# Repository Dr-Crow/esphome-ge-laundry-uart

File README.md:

# ESPHome GE Laundry UART

Local Home Assistant control and monitoring for compatible GE appliances through ESPHome and the appliance's GEA serial bus.

> [!WARNING]
> The appliance uses an 8P8C modular connector that looks like Ethernet, but it is **not Ethernet**. Do not connect it to network equipment.

**Scanned a Rev 3K, 3L or 3M board?** Match the revision printed on the carrier and the C3 or C6 marking on the XIAO. Unplug the appliance cable before attaching USB. The compact boards are review prototypes. [Open the compact firmware and service guide](https://github.com/Dr-Crow/esphome-ge-laundry-uart/blob/90f50558ca8f220444624ddab47f50d685d8c828/firmware/shared-rev3c/README.md)

The project began as an effort to integrate a GE washer and dryer with Home Assistant. An ESP32 powered by the appliance communication port reports information such as remaining time and cycle completion through ESPHome. Early work involved researching the GEA2 and GEA3 protocols and the U+ Connect module; later, [GE Appliances](https://github.com/geappliances) and [FirstBuild](https://firstbuild.com/inventions/home-assistant-adapter/) published additional hardware and protocol information. The maintained ESPHome implementation now lives in [mguaylam/esphome-gea](https://github.com/mguaylam/esphome-gea), while this repository provides compatible hardware, reference configurations, manufacturing files, and enclosures.

## Getting started

### I already have a board

For Rev 2.x, follow the [firmware setup guide](firmware/README.md) to choose a GEA2 or GEA3 configuration, flash the board, connect it to Home Assistant, and check the status LEDs. The [Rev 2 enclosure](case/rev2/README.md) includes ready-to-print files.

### I want to order a board

Start with [PCB Rev 2.2](pcb/rev2.2/README.md), then follow the [step-by-step ordering guide](pcb/ORDERING.md). Rev 2.2 corrects the known Rev 2.0 and Rev 2.1 board-file problems.

**Current status:** Rev 2.2 is the recommended manufacturing candidate; physical testing is still pending. A JLCPCB quote checked on September 19, 2026 was **$78.07 before shipping and tax for five fully assembled boards**, or about **$15.61 per board**. Prices and component availability can change.

Older boards and the complete change history are listed in the [PCB revision index](pcb/README.md). Hardware contributors should also read the [contribution guide](CONTRIBUTING.md).

## Related projects

- [GE Appliances organization](https://github.com/geappliances)
- [FirstBuild Home Assistant adapter](https://firstbuild.com/inventions/home-assistant-adapter/)
- [puddly/casserole](https://github.com/puddly/casserole)
- [GEMakers/green-bean](https://github.com/GEMakers/green-bean)
- [doitaljosh/gea-interface-board](https://github.com/doitaljosh/gea-interface-board)
- [doitaljosh/ge-appliances-re](https://github.com/doitaljosh/ge-appliances-re)
- [doitaljosh/geabus-documentation](https://github.com/doitaljosh/geabus-documentation)
- [simbaja/gehome](https://github.com/simbaja/gehome)
- [GE Appliances Home Assistant adapter](https://github.com/geappliances/home-assistant-adapter)
- [GE Appliances Home Assistant examples](https://github.com/geappliances/home-assistant-examples)
- [GE Appliances Home Assistant bridge](https://github.com/geappliances/home-assistant-bridge)

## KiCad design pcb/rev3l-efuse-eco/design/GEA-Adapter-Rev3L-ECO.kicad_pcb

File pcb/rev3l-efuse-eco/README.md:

# Rev 3L-E shared eFuse output bypass study

Experimental 65 × 30 mm carrier for isolated prototype evaluation. The underside is marked **3L-E / PROTOTYPE**. Use 3L-E to evaluate one relatively inexpensive change on the full-diagnostics carrier. The shared capacitor still has two vias in each output path. Electrical qualification, factory review and a 3L-E quote remain open.

[Native KiCad project](design/GEA-Adapter-Rev3L-ECO.kicad_pro) · [Schematic](design/GEA-Adapter-Rev3L-ECO.kicad_sch) · [Board](design/GEA-Adapter-Rev3L-ECO.kicad_pcb) · [Top CAM](evidence/cam-top.png) · [Bottom CAM](evidence/cam-bottom.png)

## What changed

C31 adds a 10 µF, 50 V, 1206 Samsung CL31A106KBHNNNE between the common protected input and ground. It uses C9’s existing C13585 SKU. C9 and C10 remain at the buck. R18 and R33 moved, with their original values. The board retains all 3L probe points, J7, signal selectors, both power inputs, front-only placement and the original outline. The two probe labels affected by placement moved with no reduction in text size.

| Center-to-center PCB route | U9 | U10 |
| --- | ---: | ---: |
| Previous closest fitted output capacitor C9, straight-line lower bound | 24.74 mm | 18.24 mm |
| New route from OUT pin 6 to C31 positive, horizontal copper including travel in end lands | 8.29 mm | 7.73 mm |
| Vias in this route | 2 | 2 |
| GND pin 8 to its nearest connected ground via | 1.94 mm | 2.43 mm |
| Plane-path straight-line lower bound between that via and C31’s ground via | 4.37 mm | 5.91 mm |

C31’s ground land reaches its ground via in 1.27 mm. Horizontal lengths exclude barrel depth. Ground current spreads through filled copper. These geometrical measurements establish proximity only. TI recommends local transient suppression at OUT. The residual two-via loop on each channel makes a separate capacitor per output preferable if the shared part does not keep both pins within their transient limits. [TI TPS25947, sections 5.1 and 8.3.1](https://www.ti.com/lit/ds/symlink/tps25947.pdf)

The +5 V detour adds 0.205 mm at the original 0.90 mm width on In2. This adds about 0.26 mΩ at 15.2 µm finished copper and 20 °C, or 0.16 mV at 0.60 A, using 1.724×10⁻⁸ Ω·m. The existing BOOT trace adds 0.027 mm at its original 0.205 mm width. Small sections of the receiver, input-overvoltage sense and priority-control signals were rerouted. The inner ground pours were refilled. The original rail-screen and mesh results belong to their original boards.

## Capacitance and qualification

Samsung’s 25 °C, 1 kHz, 1 V measurement curve gives typical effective capacitance of 3.386 µF at 12 V, 2.548 µF at 15 V, 1.898 µF at 18.85 V and 1.794 µF at 19.673 V by linear interpolation. The last voltage is a divider screen using the 1.223 V maximum rising OVLO threshold, 1.01 MΩ upper resistor, 67.32 kΩ lower resistor and 100 nA pin leakage. Handover, Q1 on the auxiliary divider and input-step overshoot require separate checks. Temperature, tolerance, aging and measurement amplitude can affect the installed capacitance. [Samsung characteristics](https://product.samsungsem.com/mlcc/CL31A106KBHNNN.do) · [TI electrical characteristics](https://www.ti.com/lit/ds/symlink/tps25947.pdf#page=9)

- On an isolated, current-limited fixture, measure the effective capacitance at operating bias and temperature. Capture each OUT at its IC ground with low-inductance probing during short-circuit interruption and hot-plug, including cable impedance and the highest enabled input. Record amplitude and duration. Design for margin to the continuous and transient absolute limits. TI’s −0.8 V OUT exception applies only below 1 µs.
- Check PIN1-only and PIN3-only start, priority transfer in both directions, a weak input still inside the voltage window, converter startup and module resets with both XIAO variants. Include the added charge taken by C31. R34/R41 set approximately 1.01 A nominal ILIM. The 0.60 A scenario is a load screen. AUXOFF indicates valid priority input after startup and can remain asserted during load overcurrent or thermal shutdown.
- Keep the entire appliance harness disconnected during USB programming. JP3 opens the D11 buck feed. The data steering paths and common ground remain. U11 is **ProTek SRV05-4-P-T7, C85364**. Its native datasheet link was corrected. J1 pins 4, 5 and 7 reach its steering diodes before the external series resistors. A powered data line can raise the module 5 V rail even with JP3 cut. Characterize each signal alone and together using representative source impedances and an initially unpowered carrier. Measure rail rise and injection current before any connector or protection redesign. See the separate data-line options for the residual pull-up paths and unqualified floating-REF proposal. [ProTek datasheet](https://www.lcsc.com/datasheet/C85364.pdf) · [Data-line protection choices](../compact-review/DATA-LINE-PROTECTION.md)
- Check USB-only cold attach on both modules. C11 and the five 100 nF capacitors contribute 10.5 µF nominal before the module’s load. D18 and D20 protect raw inputs upstream of the eFuses. A shorted TVS or sustained reversed harness depends on source-side current limiting. Check enclosed temperature, C3 antenna-lead routing, C6 antenna clearance and printed-case fit on both builds.

## Assembly evidence

Compared with combined commit `c7e102aaa9c85a485478ee5c403a945064977d56`, the bill goes from 72 to 73 fitted references and stays at 32 distinct LCSC codes. All 73 placements are on top. Only R18 and R33 change amongst previously fitted placements. Five fully assembled boards add five capacitor placements, with no additional distinct feeder SKU at these substitutions. No vendor fee or price is established for this ECO.

KiCad 9.0.9 reports zero ERC and DRC violations, zero unconnected items and zero schematic parity differences. Geometry editing used pcbnew 9.0.2. The corrected placement generator checks each fitted body center within 0.10 mm, including the rotated jack and headers. C31, R18 and R33 have body-edge distances of 9.05, 7.23 and 6.34 mm respectively. The 18 inherited bodies under JLC’s 2.5 mm guideline include the jack. Factory handling, tooling, copper tolerances and placement rotation still need the supplier’s review. [Body-edge audit](evidence/component-body-edge.csv) · [ERC](evidence/ERC.json) · [DRC and parity](evidence/DRC.json)

The CAM package contains four copper layers, 180 front paste objects and zero rear paste objects. The outline and nonplated holes match the parent. Rear QR artwork decoded from the new CAM rendering to the project repository. Physical scanning, powered testing and factory acceptance remain open. Board SHA-256 is `a03f99733d337c358b6f3299e666f42263c3d8cb844dea6cbb286324a991fa12`. [CAM and placement comparison](evidence/manufacturing-comparison.json) · [Review exports](manufacturing)

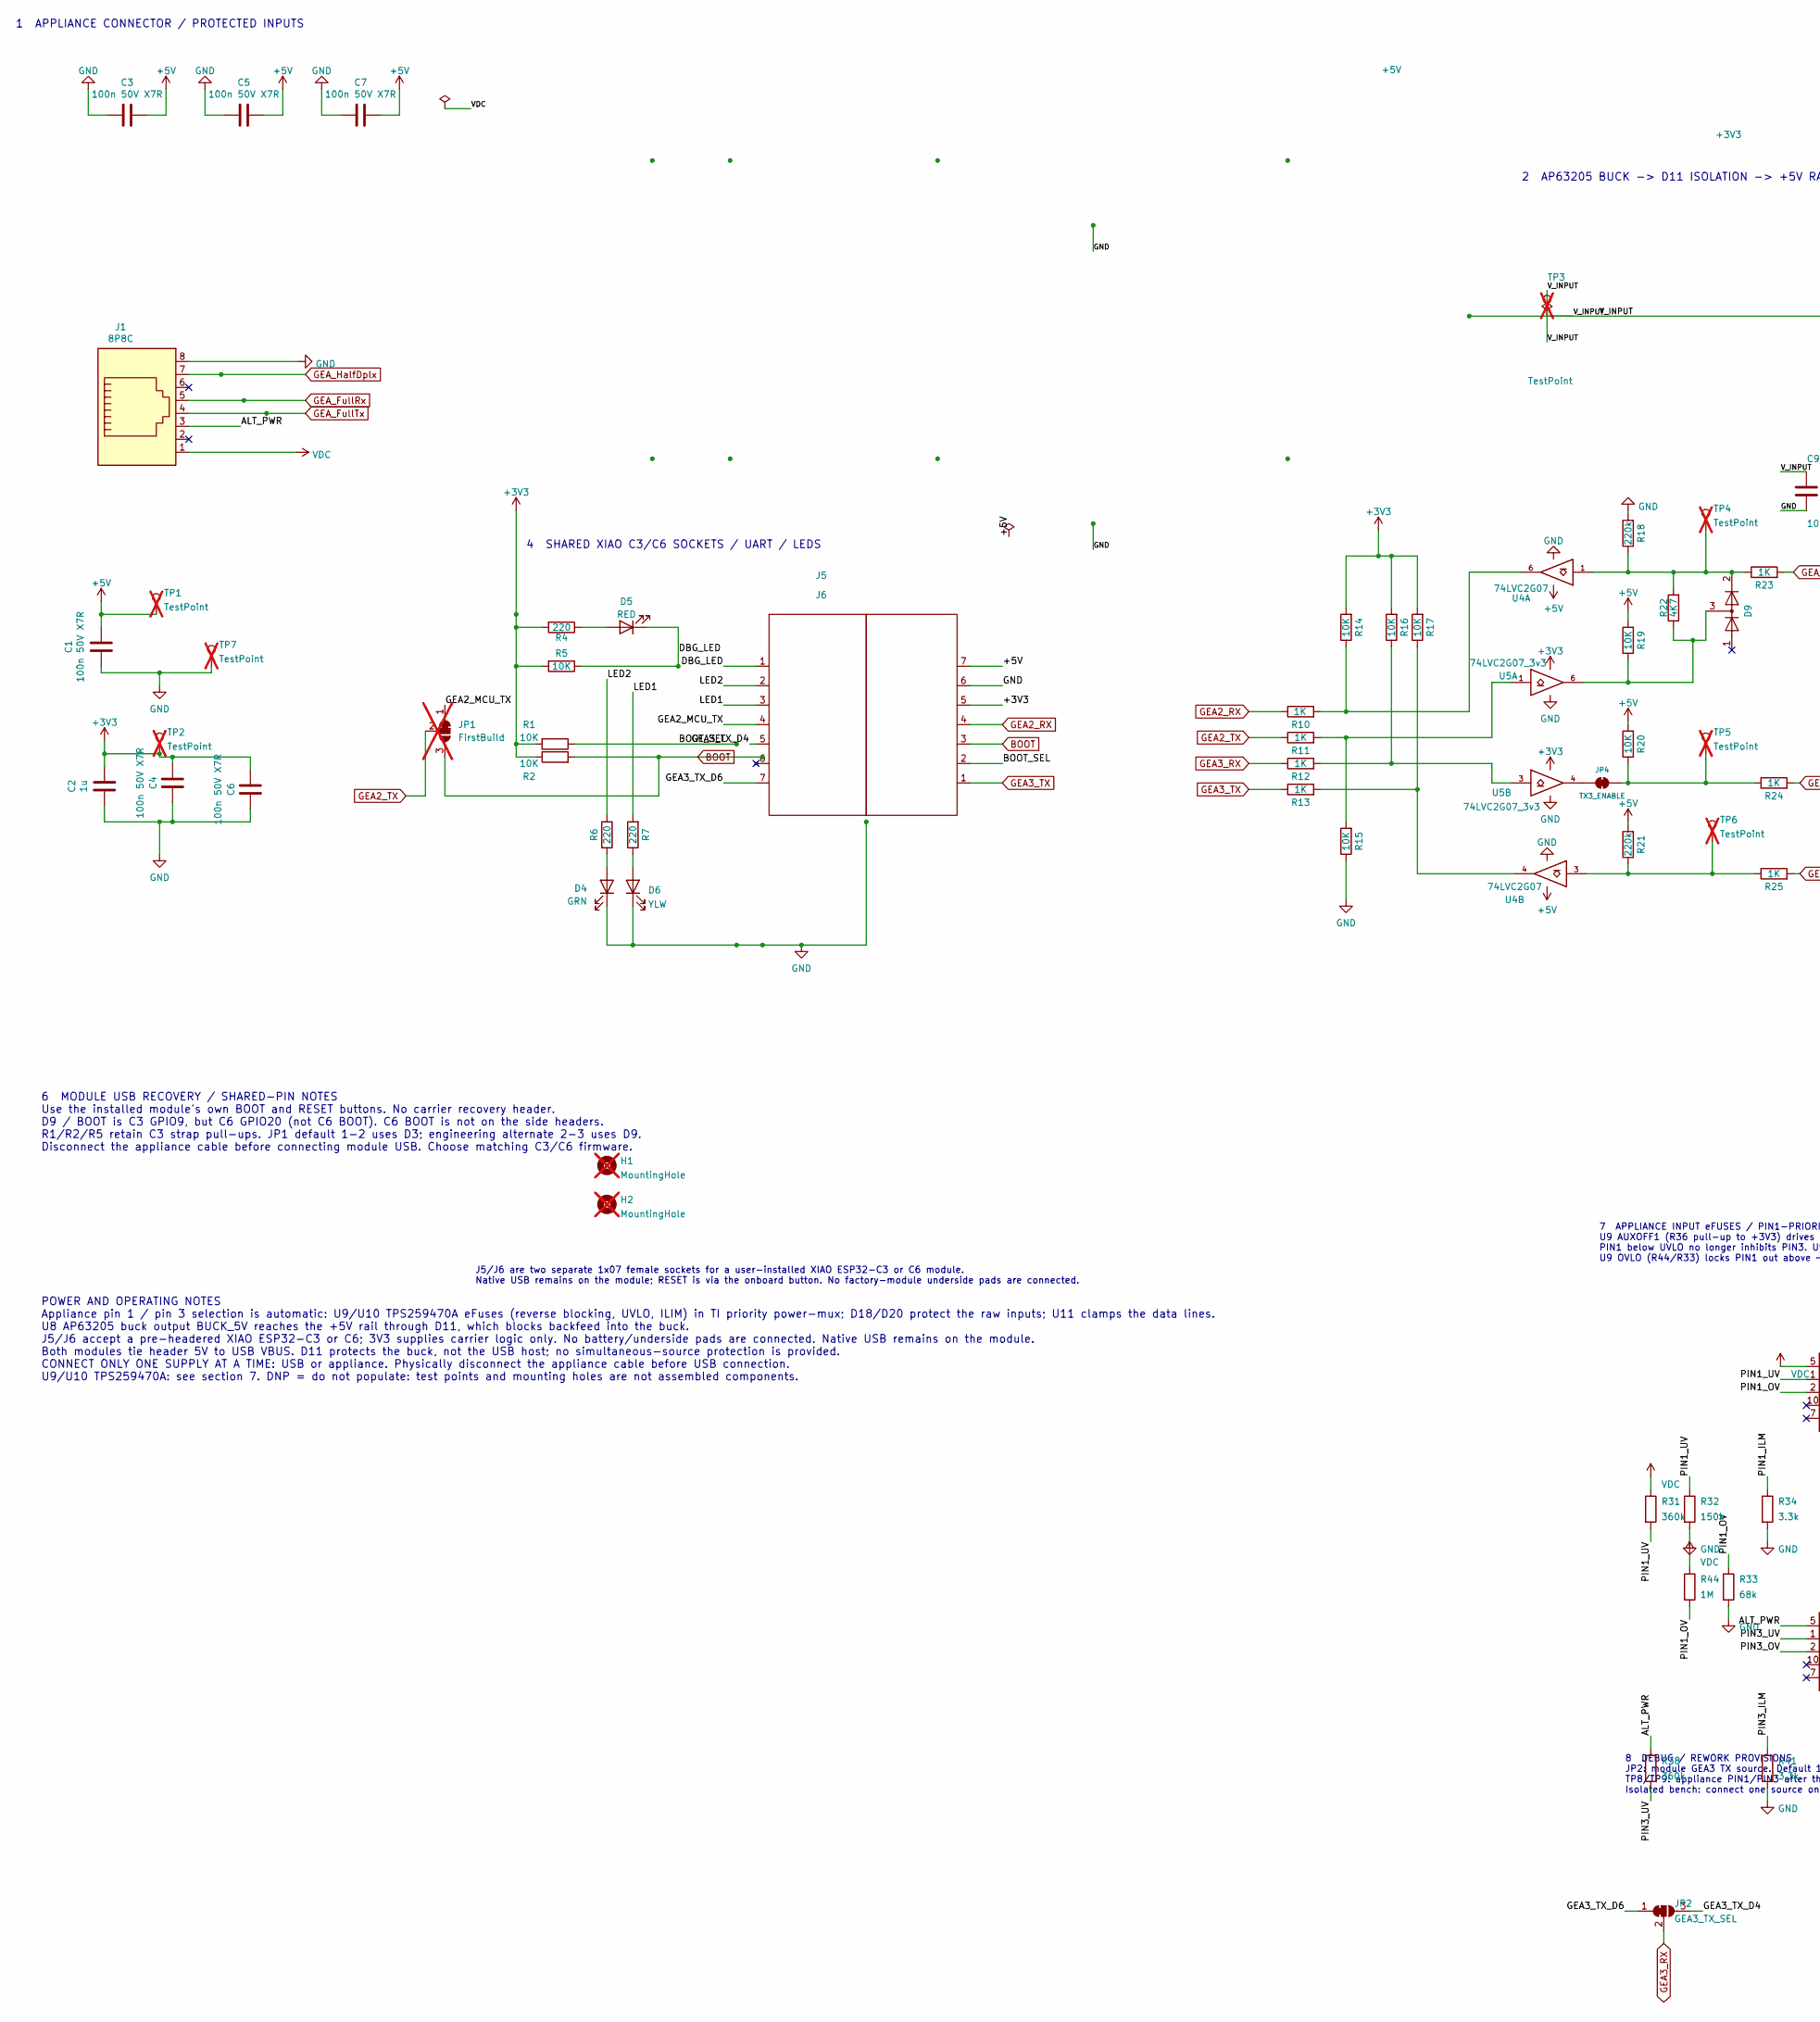
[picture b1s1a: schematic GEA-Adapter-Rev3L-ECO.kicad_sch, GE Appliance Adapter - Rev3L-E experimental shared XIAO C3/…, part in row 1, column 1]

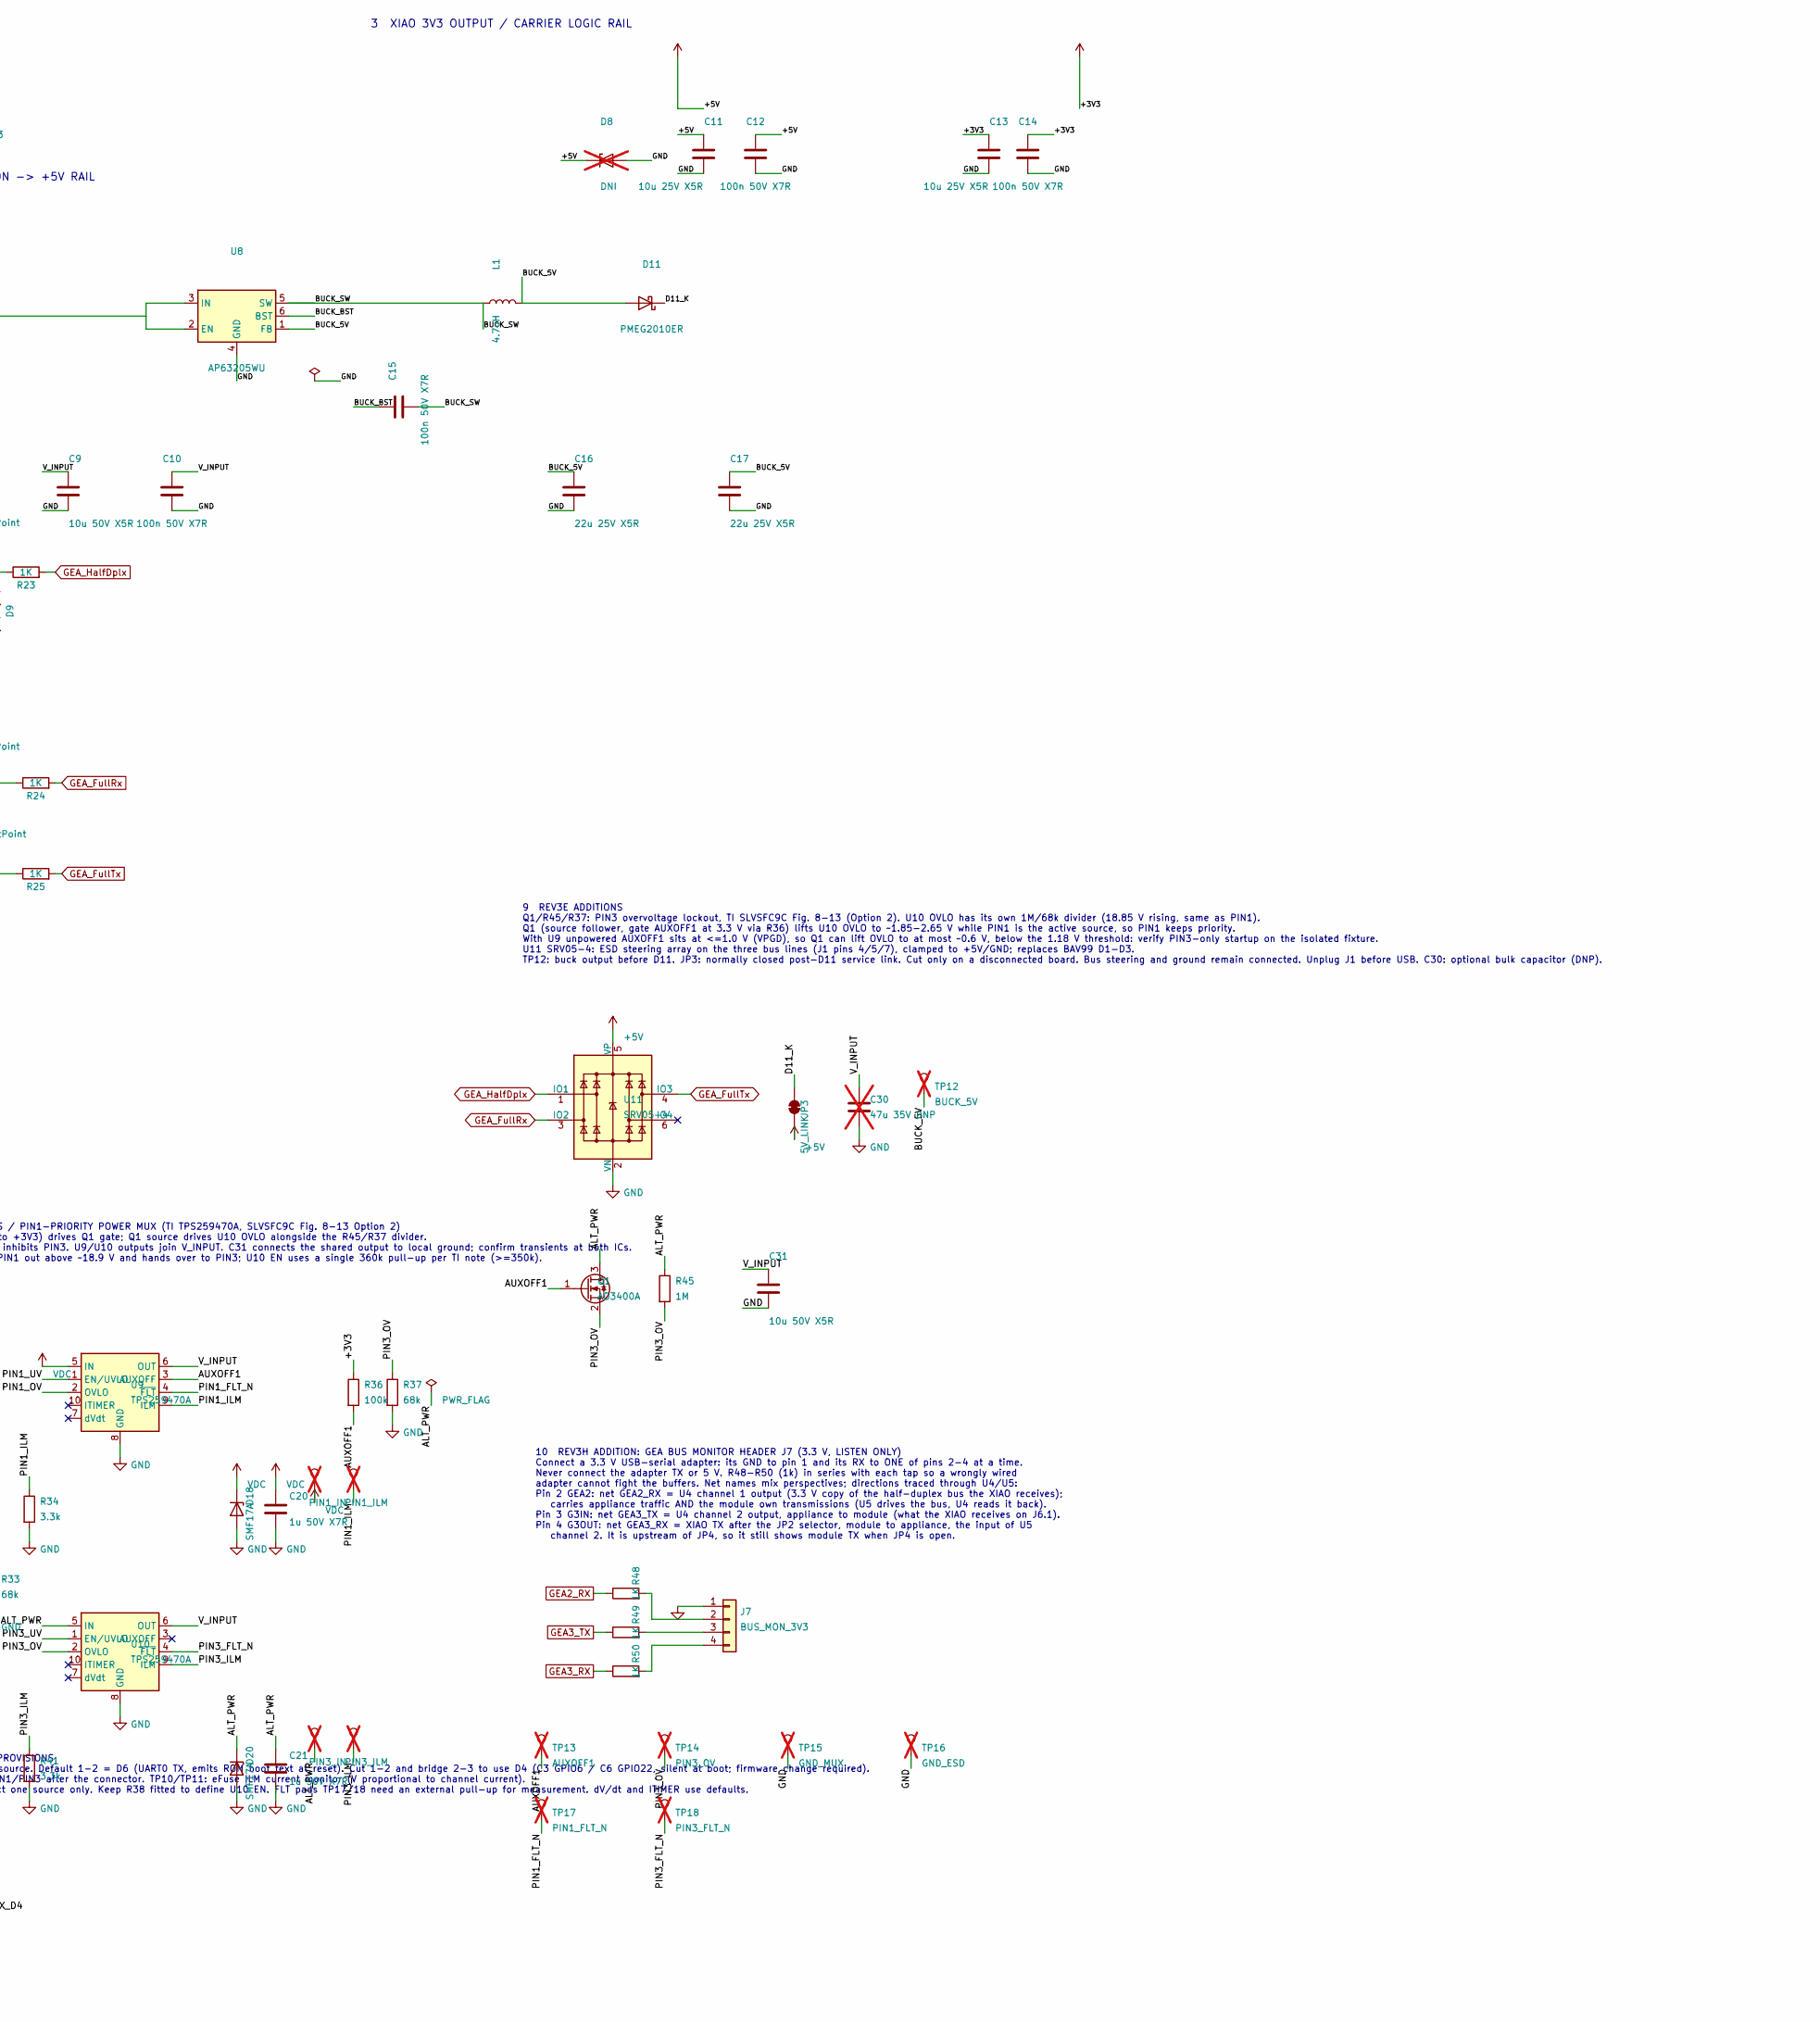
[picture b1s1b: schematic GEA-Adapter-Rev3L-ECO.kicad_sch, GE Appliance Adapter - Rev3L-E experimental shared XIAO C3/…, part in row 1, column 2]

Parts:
C1, C3, C4, C5, C6, C7, C12, C14: 100n 50V X7R; C_0603_1608Metric; MPN CC0603KRX7R9BB104; LCSC C14663
C2: 1u; C_0805_2012Metric; MPN CL21B105KBFNNNE; LCSC C28323
C9, C31: 10u 50V X5R; C_1206_3216Metric; Voltage 50V; MPN CL31A106KBHNNNE; LCSC C13585
C10, C15: 100n 50V X7R; C_0603_1608Metric; Voltage 50V; MPN CC0603KRX7R9BB104; LCSC C14663
C11, C13: 10u 25V X5R; C_0805_2012Metric; MPN CL21A106KAYNNNE; LCSC C15850
C16, C17: 22u 25V X5R; C_1206_3216Metric; Voltage 25V; Tolerance 10%; MPN CL31A226KAHNNNE; LCSC C12891
C20, C21: 1u 50V X7R; C_0805_2012Metric; MPN CL21B105KBFNNNE; LCSC C28323
C30: 47u 35V DNP; C_1210_3225Metric; not fitted
D4: GRN; LED_0805_2012Metric; MPN KT-0805G; LCSC C2297
D5: RED; LED_0805_2012Metric; MPN NCD0805R1; LCSC C84256
D6: YLW; LED_0805_2012Metric; MPN KT-0805Y; LCSC C2296
D8: DNI; D_SOD-123; not fitted
D9: BAV99; SOT-23; MPN BAV99,215; LCSC C2500
D11: PMEG2010ER; Nexperia_CFP3_SOD-123W; MPN PMEG2010ER,115; LCSC C82288
D18, D20: SMF17A; D_SOD-123F; MPN SMF17A; LCSC C2994190
H1, H2: MountingHole; MountingHole_3.2mm_M3_DIN965; not fitted
J1: 8P8C; RJ45_EVERCOM_5301-8P8C_Horizontal; MPN 5301-8P8C; LCSC C3097717
J5: Socket_XIAO_A; Socket_1x07_P2.54mm_HCTL_PM254; MPN PM254-1-07-Z-8.5; LCSC C2897370
J6: Socket_XIAO_B; Socket_1x07_P2.54mm_HCTL_PM254; MPN PM254-1-07-Z-8.5; LCSC C2897370
J7: BUS_MON_3V3; PinHeader_1x04_P2.54mm_Vertical; MPN PZ254V-11-04P; LCSC C492403
JP1: FirstBuild; SolderJumper-3_P1.3mm_Bridged12_RoundedPad1.0x1.5mm_NumberL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; not fitted
JP2: GEA3_TX_SEL; SolderJumper-3_P1.3mm_Bridged12_RoundedPad1.0x1.5mm_NumberL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
JP3: 5V_LINK; ServiceLink_NC_P2.54mm
JP4: TX3_ENABLE; SignalLink_NC_P1.8mm
L1: 4.7uH; L_Sunlord_SWPA5040S; MPN SWPA5040S4R7NT; LCSC C305174
Q1: AO3400A; SOT-23; MPN AO3400A; LCSC C20917
R1, R2, R5, R14, R15, R16, R17, R19, R20: 10K; R_0805_2012Metric; MPN 0805W8F1002T5E; LCSC C17414
R4, R6, R7: 220; R_0805_2012Metric; MPN 0805W8F2200T5E; LCSC C17557
R10, R11, R12, R13, R23, R24, R25: 1K; R_0805_2012Metric; MPN 0805W8F1001T5E; LCSC C17513
R18, R21: 220k; R_0805_2012Metric; MPN 0805W8F2203T5E; LCSC C17556
R22: 4K7; R_0805_2012Metric; MPN 0805W8F4701T5E; LCSC C17673
R31, R38: 360k; R_0603_1608Metric; MPN 0603WAF3603T5E; LCSC C23146
R32: 150k; R_0603_1608Metric; MPN 0603WAF1503T5E; LCSC C22807
R33, R37: 68k; R_0603_1608Metric; MPN 0603WAF6802T5E; LCSC C23231
R34, R41: 3.3k; R_0603_1608Metric; MPN 0603WAF3301T5E; LCSC C22978
R36: 100k; R_0603_1608Metric; MPN 0603WAF1003T5E; LCSC C25803
R44, R45: 1M; R_0603_1608Metric; MPN 0603WAF1004T5E; LCSC C22935
R48, R49, R50: 1K; R_0603_1608Metric; MPN 0603WAF1001T5E; LCSC C21190
TP1, TP2, TP3: TestPoint; TestPoint_Pad_D2.0mm; not fitted
TP4, TP5, TP6, TP7: TestPoint; TestPoint_THTPad_D2.0mm_Drill1.0mm; not fitted
TP8: PIN1_IN; TestPoint_Pad_D1.0mm; not fitted
TP9: PIN3_IN; TestPoint_Pad_D1.0mm; not fitted
TP10: PIN1_ILM; TestPoint_Pad_D1.0mm; not fitted
TP11: PIN3_ILM; TestPoint_Pad_D1.0mm; not fitted
TP12: BUCK_5V; TestPoint_Pad_D1.0mm; not fitted
TP13: AUXOFF1; TestPoint_Pad_D1.0mm; not fitted
TP14: PIN3_OV; TestPoint_Pad_D1.0mm; not fitted
TP15: GND_MUX; TestPoint_THTPad_D1.5mm_Drill0.7mm; not fitted
TP16: GND_ESD; TestPoint_Pad_D1.0mm; not fitted
TP17: PIN1_FLT_N; TestPoint_Pad_D1.0mm; not fitted
TP18: PIN3_FLT_N; TestPoint_Pad_D1.0mm; not fitted
U4: 74LVC2G07; SOT-23-6; MPN 74LVC2G07W6-7; LCSC C151607
U5: 74LVC2G07_3v3; SOT-23-6; MPN 74LVC2G07W6-7; LCSC C151607
U8: AP63205WU; TSOT-23-6; MPN AP63205WU-7; LCSC C2071056
U9, U10: TPS259470A; TI_RPW0010A_VQFN-HR-10_2x2mm; MPN TPS259470ARPWR; LCSC C3662799
U11: SRV05-4; SOT-23-6; MPN SRV05-4-P-T7; LCSC C85364

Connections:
+3V3: C2.1, C4.2, C6.2, C13.1, C14.2, J6.5 (3V3_OUT), R1.2, R2.1, R4.2, R5.2, R14.2, R16.2, R17.2, R36.1, TP2.1, U5.5 (+3V3)
+5V: C1.1, C3.1, C5.1, C7.1, C11.1, C12.2, D8.1 (K), J6.7 (VBUS), JP3.2 (B), R19.2, R20.2, R21.2, TP1.1, U4.5 (VCC), U11.5 (VP)
/ALT_PWR: C21.1, D20.1 (K), J1.3, Q1.3 (D), R38.1, R45.1, TP9.1, U10.5 (IN)
/AUXOFF1: Q1.1 (G), R36.2, TP13.1, U9.3 (AUXOFF)
/BOOT_SEL: J6.2 (BOOT_SEL), R1.1
/BUCK_5V: C16.1, C17.1, D11.2 (A), L1.2, TP12.1, U8.1 (FB)
/BUCK_BST: C15.1, U8.6 (BST)
/BUCK_SW: C15.2, L1.1, U8.5 (SW)
/D11_K: D11.1 (K), JP3.1 (A)
/DBG_LED: D5.1 (K), J5.1 (DBG_LED), R5.1
/GEA2_MCU_TX: J5.4 (GEA2_MCU_TX), JP1.1 (A)
/GEA3_TX_D4: J5.5 (D4_NC), JP2.3 (B)
/GEA3_TX_D6: J5.7 (GEA3_RX), JP2.1 (A)
/LED1: J5.3 (LED1), R7.2
/LED2: J5.2 (LED2), R6.1
/PIN1_FLT_N: TP17.1, U9.4 (~FLT)
/PIN1_ILM: R34.1, TP10.1, U9.9 (ILM)
/PIN1_OV: R33.1, R44.2, U9.2 (OVLO)
/PIN1_UV: R31.2, R32.1, U9.1 (EN/UVLO)
/PIN3_FLT_N: TP18.1, U10.4 (~FLT)
/PIN3_ILM: R41.1, TP11.1, U10.9 (ILM)
/PIN3_OV: Q1.2 (S), R37.1, R45.2, TP14.1, U10.2 (OVLO)
/PIN3_UV: R38.2, U10.1 (EN/UVLO)
/V_INPUT: C9.1, C10.2, C30.1, C31.1, TP3.1, U8.2 (EN), U8.3 (IN), U9.6 (OUT), U10.6 (OUT)
BOOT: J6.3 (BOOT), JP1.3 (B), R2.2
GEA2_RX: J6.4 (GEA2_RX), R10.1, R48.1
GEA2_TX: JP1.2 (C), R11.1
GEA3_RX: JP2.2 (C), R12.1, R50.1
GEA3_TX: J6.1 (GEA3_TX), R13.1, R49.1
GEA_FullRx: J1.5, R24.2, U11.3 (IO2)
GEA_FullTx: J1.4, R25.2, U11.4 (IO3)
GEA_HalfDplx: J1.7, R23.2, U11.1 (IO1)
GND: C1.2, C2.2, C3.2, C4.1, C5.2, C6.1, C7.2, C9.2, C10.1, C11.2, C12.1, C13.2, C14.1, C16.2, C17.2, C20.2, C21.2, C30.2, C31.2, D4.1 (K), D6.1 (K), D8.2 (A), D18.2 (A), D20.2 (A), J1.8, J6.6 (GND), J7.1, R15.1, R18.2, R32.2, R33.2, R34.2, R37.2, R41.2, TP7.1, TP15.1, TP16.1, U4.2 (GND), U5.2 (GND), U8.4 (GND), U9.8 (GND), U10.8 (GND), U11.2 (VN)
unnamed: D4.2 (A), R6.2
unnamed: D5.2 (A), R4.1
unnamed: D6.2 (A), R7.1
unnamed: D9.3 (K), R19.1, R22.1, U5.6
unnamed: D9.2 (A), R18.1, R22.2, R23.1, TP4.1, U4.1
unnamed: J7.2, R48.2
unnamed: J7.3, R49.2
unnamed: J7.4, R50.2
unnamed: JP4.1 (A), U5.4
unnamed: JP4.2 (B), R20.1, R24.1, TP5.1
unnamed: R10.2, R14.1, U4.6
unnamed: R11.2, R15.2, U5.1
unnamed: R12.2, R16.1, U5.3
unnamed: R13.2, R17.1, U4.4
unnamed: R21.1, R25.1, TP6.1, U4.3
VDC: C20.1, D18.1 (K), J1.1, R31.1, R44.1, TP8.1, U9.5 (IN)

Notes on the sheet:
1 APPLIANCE CONNECTOR / PROTECTED INPUTS
2 AP63205 BUCK -> D11 ISOLATION -> +5V RAIL
3 XIAO 3V3 OUTPUT / CARRIER LOGIC RAIL
4 SHARED XIAO C3/C6 SOCKETS / UART / LEDS
6 MODULE USB RECOVERY / SHARED-PIN NOTES Use the installed module's own BOOT and RESET buttons. No carrier recovery header. D9 / BOOT is C3 GPIO9, but C6 GPIO20 (not C6 BOOT). C6 BOOT is not on the side headers. R1/R2/R5 retain C3 strap pull-ups. JP1 default 1-2 uses D3; engineering alternate 2-3 u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
POWER AND OPERATING NOTES Appliance pin 1 / pin 3 selection is automatic: U9/U10 TPS259470A eFuses (reverse blocking, UVLO, ILIM) in TI priority power-mux; D18/D20 protect the raw inputs; U11 clamps the data lines. U8 AP63205 buck output BUCK_5V reaches the +5V rail through D11, which blocks backfe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
J5/J6 are two separate 1x07 female sockets for a user-installed XIAO ESP32-C3 or C6 module. Native USB remains on the module; RESET is via the onboard button. No factory-module underside pads are connected.
7 APPLIANCE INPUT eFUSES / PIN1-PRIORITY POWER MUX (TI TPS259470A, SLVSFC9C Fig. 8-13 Option 2) U9 AUXOFF1 (R36 pull-up to +3V3) drives Q1 gate; Q1 source drives U10 OVLO alongside the R45/R37 divider. PIN1 below UVLO no longer inhibits PIN3. U9/U10 outputs join V_INPUT. C31 connects the shared out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
8 DEBUG / REWORK PROVISIONS JP2: module GEA3 TX source. Default 1-2 = D6 (UART0 TX, emits ROM boot text at reset). Cut 1-2 and bridge 2-3 to use D4 (C3 GPIO6 / C6 GPIO22, silent at boot; firmware change required). TP8/TP9: appliance PIN1/PIN3 after the connector. TP10/TP11: eFuse ILM current monito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
9 REV3E ADDITIONS Q1/R45/R37: PIN3 overvoltage lockout, TI SLVSFC9C Fig. 8-13 (Option 2). U10 OVLO has its own 1M/68k divider (18.85 V rising, same as PIN1). Q1 (source follower, gate AUXOFF1 at 3.3 V via R36) lifts U10 OVLO to ~1.85-2.65 V while PIN1 is the active source, so PIN1 keeps priority. W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
10 REV3H ADDITION: GEA BUS MONITOR HEADER J7 (3.3 V, LISTEN ONLY) Connect a 3.3 V USB-serial adapter: its GND to pin 1 and its RX to ONE of pins 2-4 at a time. Never connect the adapter TX or 5 V. R48-R50 (1k) in series with each tap so a wrongly wired adapter cannot fight the buffers. Net names mi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

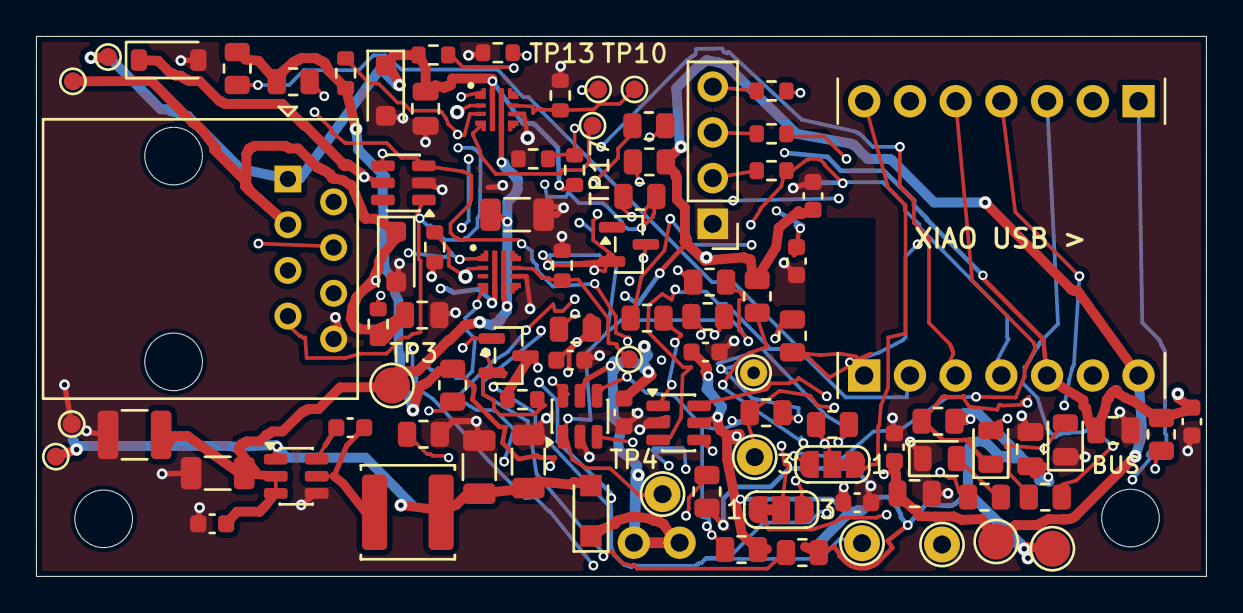
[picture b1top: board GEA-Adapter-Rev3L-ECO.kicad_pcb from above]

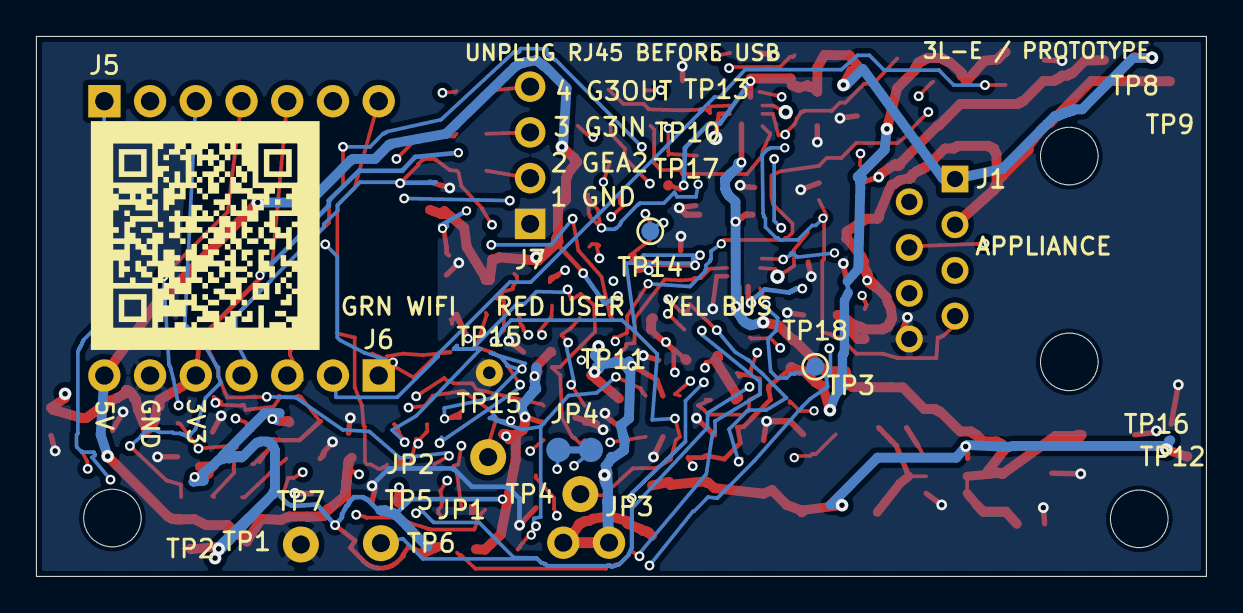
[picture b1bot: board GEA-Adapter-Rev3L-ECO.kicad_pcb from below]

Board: 4 copper layers, 65.0 x 30.0 mm, 99 parts (3 on the bottom side), 49 nets.
